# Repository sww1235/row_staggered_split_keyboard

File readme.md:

# Row Staggered Split Keyboard

The Row Staggered Split keyboard is for typists who need to maintain their muscle memory
of standard ANSI layout 104 key keyboards, but also would like a split keyboard.

This keyboard consists of 4 large components that are completely independant but augment each other:

- Left hand keyboard
- Right hand keyboard
- Navigation cluster
- Numpad

All components of the keyboard have independant KB2040 controllers and so do
not use the split keyboard functionality in QMK.

All keyboard components have per key RGB LED matrix lighting.

These keyboards have first class support in QMK. VIA/VIAL support is not
available currently as I do not use it, but there is nothing restricting its
addition in the future.

## Left Hand Keyboard

This is the left side of a standard ANSI 104 key layout keyboard, including the
`B` key. The `ESC` key and `F1`-`F4` are in their usual locations, and
`F5`-`F10` are in an additional row to the left of the `Tab`/`Shift`/`Caps
Lock` keys.

A `FN` key is included in the bottom right to provide alternate functionality
such as media keys, etc which are currently unimplemented. The `FN` layout
currently has additional keys defined for control of the RGB matrix, including
the `EE_CLR` key. This is needed to clear the keyboards EEPROM, primarily for
changing the RGB LED lighting effects.

## Right Hand Keyboard

This is the right side of a standard ANSI 104 key layout keyboard, including
the `B` key. As the left hand side has `F1`-`F10`, the function keys on the top
row start at `F11` and continue to `F16`, with `F17` available on the bottom
right.

A `FN` key is included in the bottom right to provide alternate functionality
such as media keys, etc which are currently unimplemented. The `FN` layout
currently has additional keys defined for control of the RGB matrix, including
the `EE_CLR` key. This is needed to clear the keyboards EEPROM, primarily for
changing the RGB LED lighting effects.

See the keyboard layouts shown below for more details.

## Navigation Cluster

This keyboard PCB is currently under developement, with PCB and key layout not finalized.

This section is the navigation cluster of standard ANSI 104 key layout
keyboards, including the `INSERT`, `DELETE`, `HOME`, `END`, `PAGE UP` and `PAGE
DOWN` keys, and the arrow cluster. 

To increase the number of function keys available, a 4th column has been added
with `F21`-`F24`, as well as the empty row between the `DELETE`/`END`/`PAGE
DOWN` keys and the arrow cluster has been filled in with `F18`-`F20`. There are
also 3 unassigned keys in the layout currently as seen in the layout images.

This section is essentially a 5 row x 4 column macro pad.

## Numpad

This keyboard PCB is currently under developement, with PCB and key layout not finalized.

This is a standard numpad layout, with some minor tweaks to the layout of the
nav cluster (numlock off) layer, and the addition of a `00` key.

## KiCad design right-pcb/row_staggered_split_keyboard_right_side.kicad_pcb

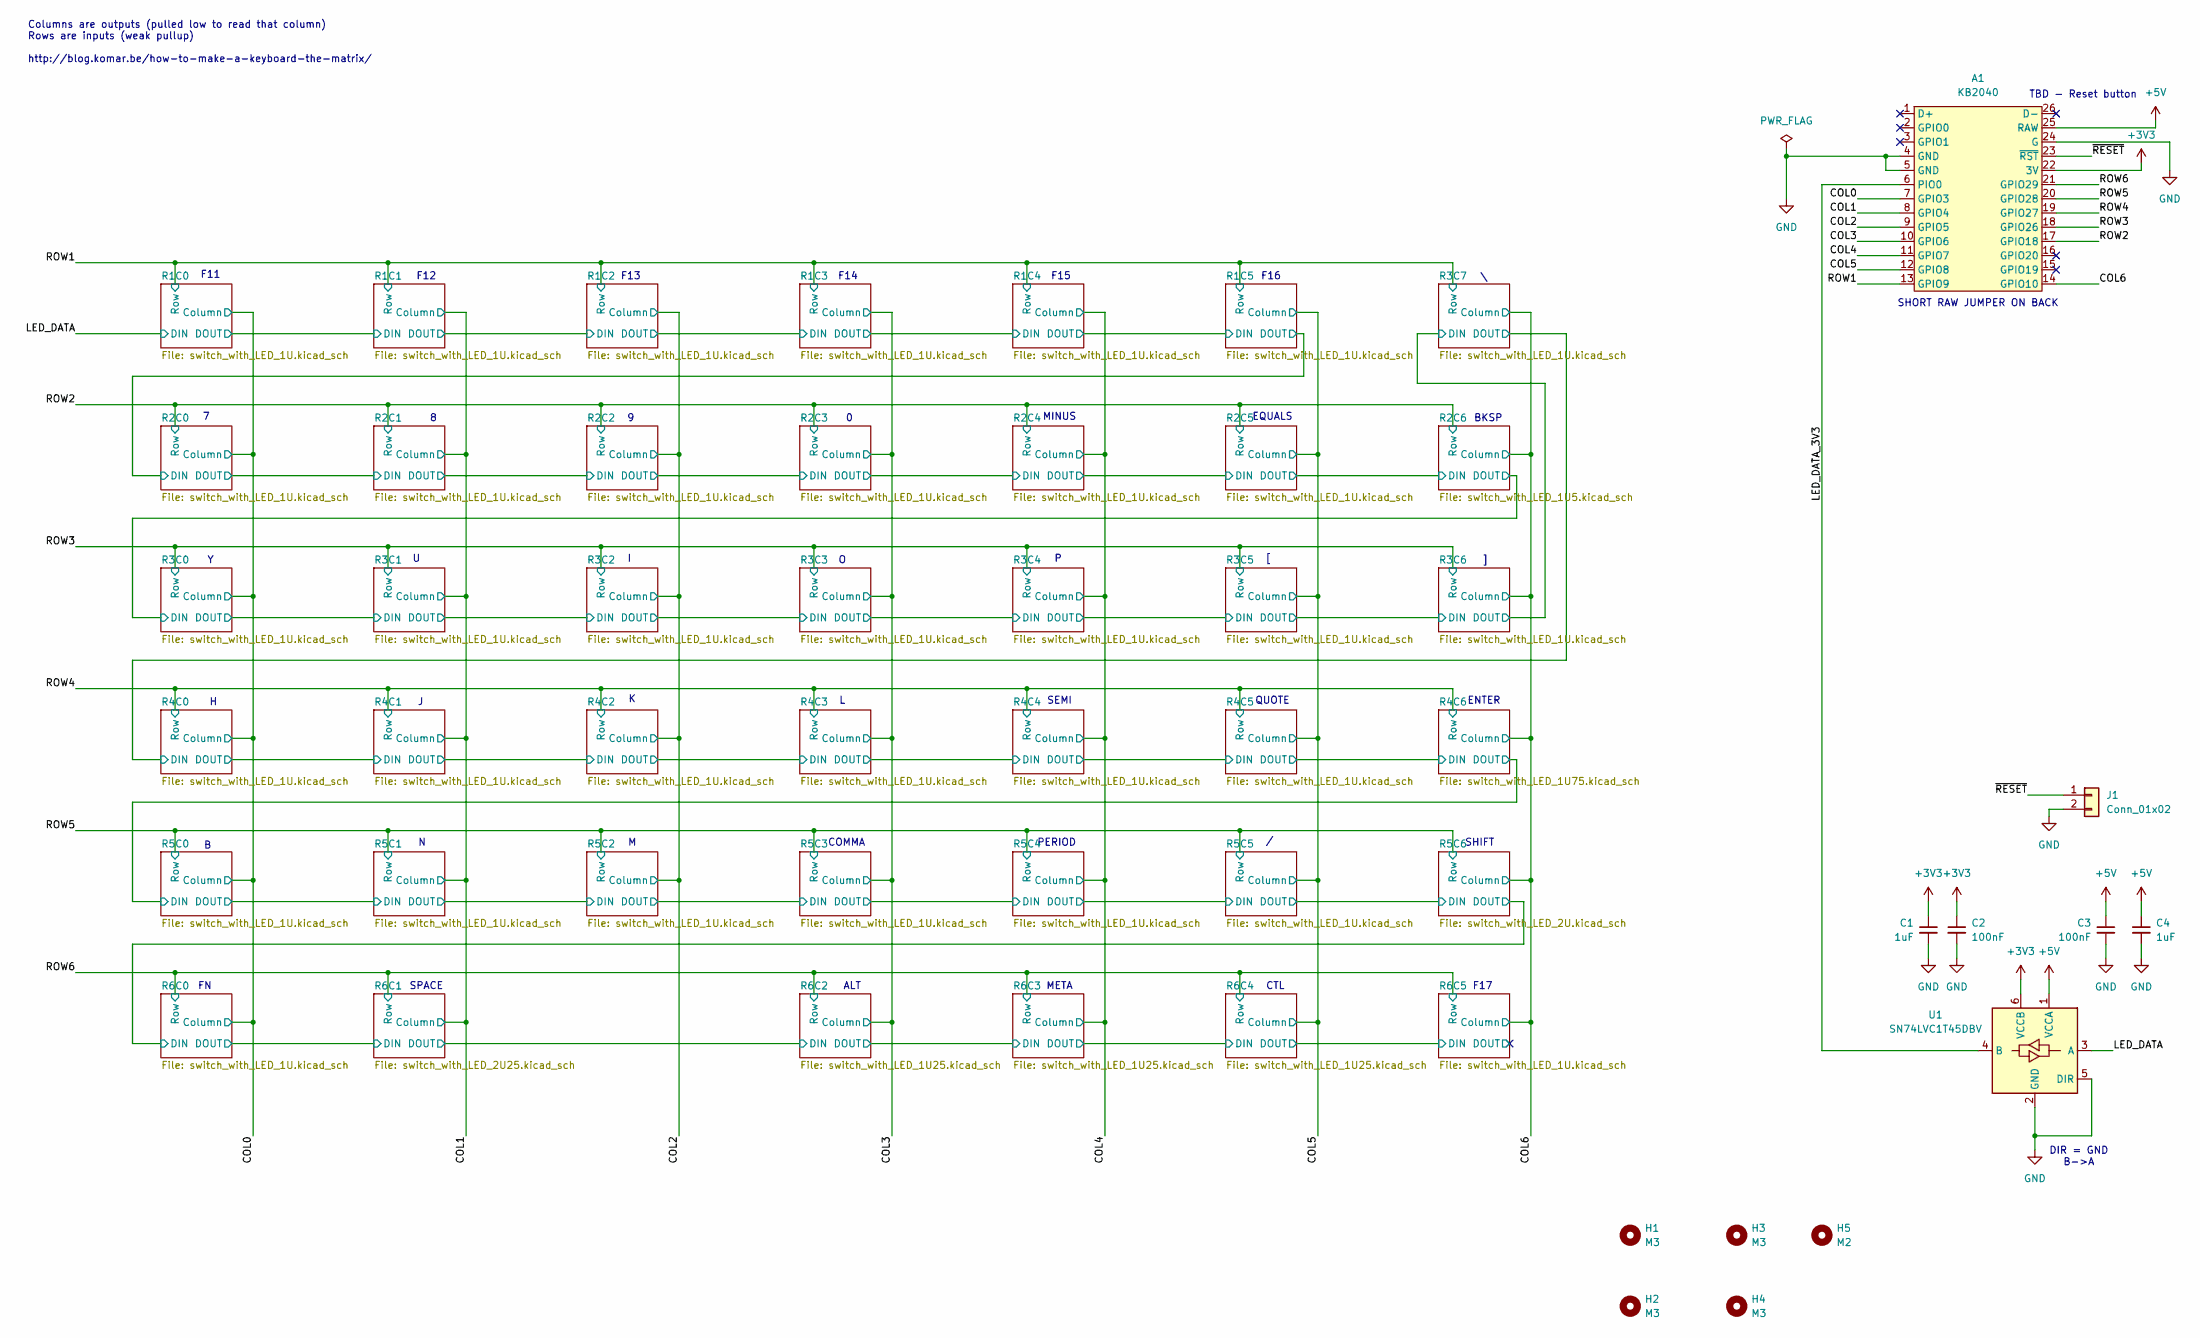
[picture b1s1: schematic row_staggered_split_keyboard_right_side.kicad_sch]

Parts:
A1: KB2040; KB2024_Socketed
C1, C4: 1uF; C_0805_2012Metric_Pad1.18x1.45mm_HandSolder
C2, C3: 100nF; C_0805_2012Metric_Pad1.18x1.45mm_HandSolder
H1, H2, H3, H4: M3; MountingHole_3.2mm_M3_ISO14580
H5: M2; MountingHole_2.2mm_M2
J1: Conn_01x02; PinSocket_1x02_P2.54mm_Vertical
U1: SN74LVC1T45DBV; SOT-23-6

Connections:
+3V3: A1.22 (3V), C1.1, C2.1, U1.6 (VCCB)
+5V: A1.25 (RAW), C3.1, C4.1, U1.1 (VCCA); also elsewhere on the board
/COL0: A1.7 (GPIO3); also elsewhere on the board
/COL1: A1.8 (GPIO4); also elsewhere on the board
/COL2: A1.9 (GPIO5); also elsewhere on the board
/COL3: A1.10 (GPIO6); also elsewhere on the board
/COL4: A1.11 (GPIO7); also elsewhere on the board
/COL5: A1.12 (GPIO8); also elsewhere on the board
/COL6: A1.14 (GPIO10); also elsewhere on the board
/LED_DATA: U1.3 (A); also elsewhere on the board
/LED_DATA_3V3: A1.6 (PIO0), U1.4 (B)
/ROW1: A1.13 (GPIO9); also elsewhere on the board
/ROW2: A1.17 (GPIO18); also elsewhere on the board
/ROW3: A1.18 (GPIO26); also elsewhere on the board
/ROW4: A1.19 (GPIO27); also elsewhere on the board
/ROW5: A1.20 (GPIO28); also elsewhere on the board
/ROW6: A1.21 (GPIO29); also elsewhere on the board
/~RESET: A1.23 (~RST), J1.1
GND: A1.4 (GND), A1.5 (GND), A1.24 (G), C1.2, C2.2, C3.2, C4.2, J1.2, U1.2 (GND), U1.5 (DIR); also elsewhere on the board

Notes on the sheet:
SHORT RAW JUMPER ON BACK
SPACE
DIR = GND B->A
ENTER
SHIFT
EQUALS
BKSP
F14
F15
META
MINUS
CTL
ALT
COMMA
QUOTE
F12
SEMI
F17
F13
F16
PERIOD
TBD - Reset button
Columns are outputs (pulled low to read that column) Rows are inputs (weak pullup) http://blog.komar.be/how-to-make-a-keyboard-the-matrix/
F11

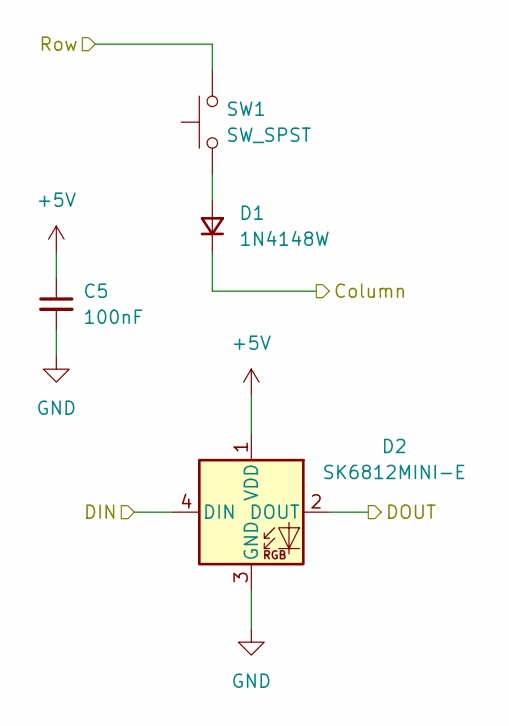
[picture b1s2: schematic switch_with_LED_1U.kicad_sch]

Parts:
C5: 100nF; C_0805_2012Metric_Pad1.18x1.45mm_HandSolder
D1: 1N4148W; D_SOD-123
D2: SK6812MINI-E; LED_SK6812MINI-E_REVERSE_MOUNT_3.2x2.8mm_P1.09mm
SW1: SW_SPST; SW_Hotswap_Kailh_MX_1.00u

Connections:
+5V: C5.1, D2.1 (VDD); also elsewhere on the board
/COL0: D1.1 (K); also elsewhere on the board
/LED_DATA: D2.4 (DIN); also elsewhere on the board
/R1C0/DOUT: D2.2 (DOUT); also elsewhere on the board
/ROW1: SW1.2; also elsewhere on the board
GND: C5.2, D2.3 (GND); also elsewhere on the board
unnamed: D1.2 (A), SW1.1

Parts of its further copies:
C6, C7, C8, C9, C10, C11, C12, C13, C14, C15, C16, C18, C19, C20, C21, C22, C23, C24, C25, C26, C27, C28, C29, C30, C31, C33, C34, C35, C36, C37, C38, C40, C45: 100nF; C_0805_2012Metric_Pad1.18x1.45mm_HandSolder
D3, D5, D7, D9, D11, D13, D15, D17, D19, D21, D23, D27, D29, D31, D33, D35, D37, D39, D41, D43, D45, D47, D49, D51, D53, D57, D59, D61, D63, D65, D67, D71, D81: 1N4148W; D_SOD-123
D4, D6, D8, D10, D12, D14, D16, D18, D20, D22, D24, D28, D30, D32, D34, D36, D38, D40, D42, D44, D46, D48, D50, D52, D54, D58, D60, D62, D64, D66, D68, D72, D82: SK6812MINI-E; LED_SK6812MINI-E_REVERSE_MOUNT_3.2x2.8mm_P1.09mm
SW2, SW3, SW4, SW5, SW6, SW7, SW8, SW9, SW10, SW11, SW12, SW14, SW15, SW16, SW17, SW18, SW19, SW20, SW21, SW22, SW23, SW24, SW25, SW26, SW27, SW29, SW30, SW31, SW32, SW33, SW34, SW36, SW41: SW_SPST; SW_Hotswap_Kailh_MX_1.00u

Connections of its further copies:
+5V: C6.1, C7.1, C8.1, C9.1, C10.1, C11.1, C12.1, C13.1, C14.1, C15.1, C16.1, C18.1, C19.1, C20.1, C21.1, C22.1, C23.1, C24.1, C25.1, C26.1, C27.1, C28.1, C29.1, C30.1, C31.1, C33.1, C34.1, C35.1, C36.1, C37.1, C38.1, C40.1, C45.1, D4.1 (VDD), D6.1 (VDD), D8.1 (VDD), D10.1 (VDD), D12.1 (VDD), D14.1 (VDD), D16.1 (VDD), D18.1 (VDD), D20.1 (VDD), D22.1 (VDD), D24.1 (VDD), D28.1 (VDD), D30.1 (VDD), D32.1 (VDD), D34.1 (VDD), D36.1 (VDD), D38.1 (VDD), D40.1 (VDD), D42.1 (VDD), D44.1 (VDD), D46.1 (VDD), D48.1 (VDD), D50.1 (VDD), D52.1 (VDD), D54.1 (VDD), D58.1 (VDD), D60.1 (VDD), D62.1 (VDD), D64.1 (VDD), D66.1 (VDD), D68.1 (VDD), D72.1 (VDD), D82.1 (VDD); also elsewhere on the board
/COL0: D13.1 (K), D27.1 (K), D43.1 (K), D57.1 (K), D71.1 (K); also elsewhere on the board
/COL1: D3.1 (K), D15.1 (K), D29.1 (K), D45.1 (K), D59.1 (K); also elsewhere on the board
/COL2: D5.1 (K), D17.1 (K), D31.1 (K), D47.1 (K), D61.1 (K); also elsewhere on the board
/COL3: D7.1 (K), D19.1 (K), D33.1 (K), D49.1 (K), D63.1 (K); also elsewhere on the board
/COL4: D9.1 (K), D21.1 (K), D35.1 (K), D51.1 (K), D65.1 (K); also elsewhere on the board
/COL5: D11.1 (K), D23.1 (K), D37.1 (K), D53.1 (K), D67.1 (K); also elsewhere on the board
/COL6: D39.1 (K), D41.1 (K), D81.1 (K); also elsewhere on the board
/R1C0/DOUT: D4.4 (DIN); also elsewhere on the board
/R1C1/DOUT: D4.2 (DOUT), D6.4 (DIN)
/R1C2/DOUT: D6.2 (DOUT), D8.4 (DIN)
/R1C3/DOUT: D8.2 (DOUT), D10.4 (DIN)
/R1C4/DOUT: D10.2 (DOUT), D12.4 (DIN)
/R1C5/DOUT: D12.2 (DOUT), D14.4 (DIN)
/R2C0/DOUT: D14.2 (DOUT), D16.4 (DIN)
/R2C1/DOUT: D16.2 (DOUT), D18.4 (DIN)
/R2C2/DOUT: D18.2 (DOUT), D20.4 (DIN)
/R2C3/DOUT: D20.2 (DOUT), D22.4 (DIN)
/R2C4/DOUT: D22.2 (DOUT), D24.4 (DIN)
/R2C5/DOUT: D24.2 (DOUT); also elsewhere on the board
/R2C6/DOUT: D28.4 (DIN); also elsewhere on the board
/R3C0/DOUT: D28.2 (DOUT), D30.4 (DIN)
/R3C1/DOUT: D30.2 (DOUT), D32.4 (DIN)
/R3C2/DOUT: D32.2 (DOUT), D34.4 (DIN)
/R3C3/DOUT: D34.2 (DOUT), D36.4 (DIN)
/R3C4/DOUT: D36.2 (DOUT), D38.4 (DIN)
/R3C5/DOUT: D38.2 (DOUT), D40.4 (DIN)
/R3C6/DOUT: D40.2 (DOUT), D42.4 (DIN)
/R3C7/DOUT: D42.2 (DOUT), D44.4 (DIN)
/R4C0/DOUT: D44.2 (DOUT), D46.4 (DIN)
/R4C1/DOUT: D46.2 (DOUT), D48.4 (DIN)
/R4C2/DOUT: D48.2 (DOUT), D50.4 (DIN)
/R4C3/DOUT: D50.2 (DOUT), D52.4 (DIN)
/R4C4/DOUT: D52.2 (DOUT), D54.4 (DIN)
/R4C5/DOUT: D54.2 (DOUT); also elsewhere on the board
/R4C6/DOUT: D58.4 (DIN); also elsewhere on the board
/R5C0/DOUT: D58.2 (DOUT), D60.4 (DIN)
/R5C1/DOUT: D60.2 (DOUT), D62.4 (DIN)
/R5C2/DOUT: D62.2 (DOUT), D64.4 (DIN)
/R5C3/DOUT: D64.2 (DOUT), D66.4 (DIN)
/R5C4/DOUT: D66.2 (DOUT), D68.4 (DIN)
/R5C5/DOUT: D68.2 (DOUT); also elsewhere on the board
/R5C6/DOUT: D72.4 (DIN); also elsewhere on the board
/R6C0/DOUT: D72.2 (DOUT); also elsewhere on the board
/R6C4/DOUT: D82.4 (DIN); also elsewhere on the board
/R6C5/DOUT: D82.2 (DOUT)
/ROW1: SW2.2, SW3.2, SW4.2, SW5.2, SW6.2, SW21.2; also elsewhere on the board
/ROW2: SW7.2, SW8.2, SW9.2, SW10.2, SW11.2, SW12.2; also elsewhere on the board
/ROW3: SW14.2, SW15.2, SW16.2, SW17.2, SW18.2, SW19.2, SW20.2; also elsewhere on the board
/ROW4: SW22.2, SW23.2, SW24.2, SW25.2, SW26.2, SW27.2; also elsewhere on the board
/ROW5: SW29.2, SW30.2, SW31.2, SW32.2, SW33.2, SW34.2; also elsewhere on the board
/ROW6: SW36.2, SW41.2; also elsewhere on the board
GND: C6.2, C7.2, C8.2, C9.2, C10.2, C11.2, C12.2, C13.2, C14.2, C15.2, C16.2, C18.2, C19.2, C20.2, C21.2, C22.2, C23.2, C24.2, C25.2, C26.2, C27.2, C28.2, C29.2, C30.2, C31.2, C33.2, C34.2, C35.2, C36.2, C37.2, C38.2, C40.2, C45.2, D4.3 (GND), D6.3 (GND), D8.3 (GND), D10.3 (GND), D12.3 (GND), D14.3 (GND), D16.3 (GND), D18.3 (GND), D20.3 (GND), D22.3 (GND), D24.3 (GND), D28.3 (GND), D30.3 (GND), D32.3 (GND), D34.3 (GND), D36.3 (GND), D38.3 (GND), D40.3 (GND), D42.3 (GND), D44.3 (GND), D46.3 (GND), D48.3 (GND), D50.3 (GND), D52.3 (GND), D54.3 (GND), D58.3 (GND), D60.3 (GND), D62.3 (GND), D64.3 (GND), D66.3 (GND), D68.3 (GND), D72.3 (GND), D82.3 (GND); also elsewhere on the board
unnamed: D3.2 (A), SW2.1
unnamed: D5.2 (A), SW3.1
unnamed: D7.2 (A), SW4.1
unnamed: D9.2 (A), SW5.1
unnamed: D11.2 (A), SW6.1
unnamed: D13.2 (A), SW7.1
unnamed: D15.2 (A), SW8.1
unnamed: D17.2 (A), SW9.1
unnamed: D19.2 (A), SW10.1
unnamed: D21.2 (A), SW11.1
unnamed: D23.2 (A), SW12.1
unnamed: D27.2 (A), SW14.1
unnamed: D29.2 (A), SW15.1
unnamed: D31.2 (A), SW16.1
unnamed: D33.2 (A), SW17.1
unnamed: D35.2 (A), SW18.1
unnamed: D37.2 (A), SW19.1
unnamed: D39.2 (A), SW20.1
unnamed: D41.2 (A), SW21.1
unnamed: D43.2 (A), SW22.1
unnamed: D45.2 (A), SW23.1
unnamed: D47.2 (A), SW24.1
unnamed: D49.2 (A), SW25.1
unnamed: D51.2 (A), SW26.1
unnamed: D53.2 (A), SW27.1
unnamed: D57.2 (A), SW29.1
unnamed: D59.2 (A), SW30.1
unnamed: D61.2 (A), SW31.1
unnamed: D63.2 (A), SW32.1
unnamed: D65.2 (A), SW33.1
unnamed: D67.2 (A), SW34.1
unnamed: D71.2 (A), SW36.1
unnamed: D81.2 (A), SW41.1

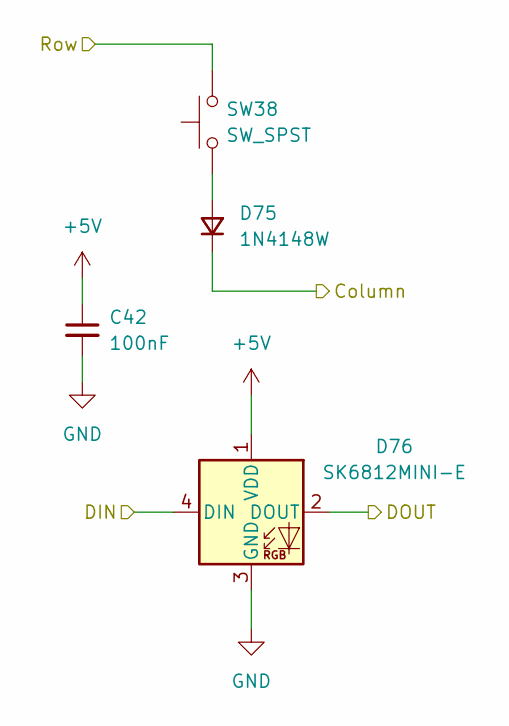
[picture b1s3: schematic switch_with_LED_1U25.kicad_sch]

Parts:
C42: 100nF; C_0805_2012Metric_Pad1.18x1.45mm_HandSolder
D75: 1N4148W; D_SOD-123
D76: SK6812MINI-E; LED_SK6812MINI-E_REVERSE_MOUNT_3.2x2.8mm_P1.09mm
SW38: SW_SPST; SW_Hotswap_Kailh_MX_1.25u

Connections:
+5V: C42.1, D76.1 (VDD); also elsewhere on the board
/COL3: D75.1 (K); also elsewhere on the board
/R6C1/DOUT: D76.4 (DIN); also elsewhere on the board
/R6C2/DOUT: D76.2 (DOUT); also elsewhere on the board
/ROW6: SW38.2; also elsewhere on the board
GND: C42.2, D76.3 (GND); also elsewhere on the board
unnamed: D75.2 (A), SW38.1

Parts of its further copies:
C43, C44: 100nF; C_0805_2012Metric_Pad1.18x1.45mm_HandSolder
D77, D79: 1N4148W; D_SOD-123
D78, D80: SK6812MINI-E; LED_SK6812MINI-E_REVERSE_MOUNT_3.2x2.8mm_P1.09mm
SW39, SW40: SW_SPST; SW_Hotswap_Kailh_MX_1.25u

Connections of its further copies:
+5V: C43.1, C44.1, D78.1 (VDD), D80.1 (VDD); also elsewhere on the board
/COL4: D77.1 (K); also elsewhere on the board
/COL5: D79.1 (K); also elsewhere on the board
/R6C2/DOUT: D78.4 (DIN); also elsewhere on the board
/R6C3/DOUT: D78.2 (DOUT), D80.4 (DIN)
/R6C4/DOUT: D80.2 (DOUT); also elsewhere on the board
/ROW6: SW39.2, SW40.2; also elsewhere on the board
GND: C43.2, C44.2, D78.3 (GND), D80.3 (GND); also elsewhere on the board
unnamed: D77.2 (A), SW39.1
unnamed: D79.2 (A), SW40.1

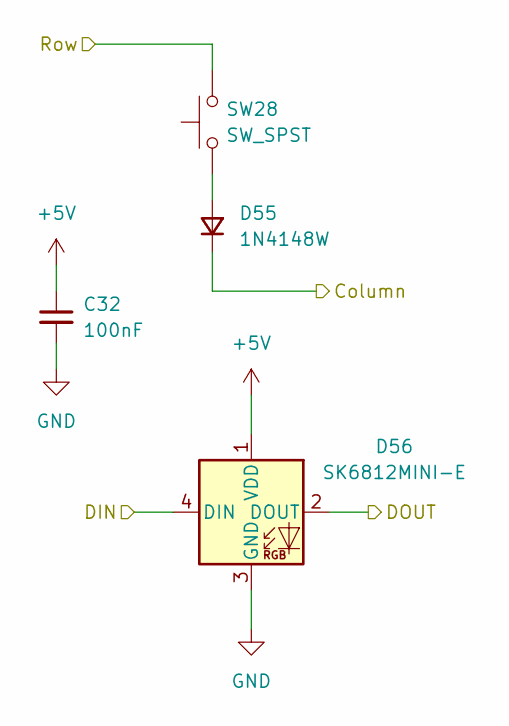
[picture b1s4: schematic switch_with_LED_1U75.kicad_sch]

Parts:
C32: 100nF; C_0805_2012Metric_Pad1.18x1.45mm_HandSolder
D55: 1N4148W; D_SOD-123
D56: SK6812MINI-E; LED_SK6812MINI-E_REVERSE_MOUNT_3.2x2.8mm_P1.09mm
SW28: SW_SPST; SW_Hotswap_Kailh_MX_1.75u

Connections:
+5V: C32.1, D56.1 (VDD); also elsewhere on the board
/COL6: D55.1 (K); also elsewhere on the board
/R4C5/DOUT: D56.4 (DIN); also elsewhere on the board
/R4C6/DOUT: D56.2 (DOUT); also elsewhere on the board
/ROW4: SW28.2; also elsewhere on the board
GND: C32.2, D56.3 (GND); also elsewhere on the board
unnamed: D55.2 (A), SW28.1

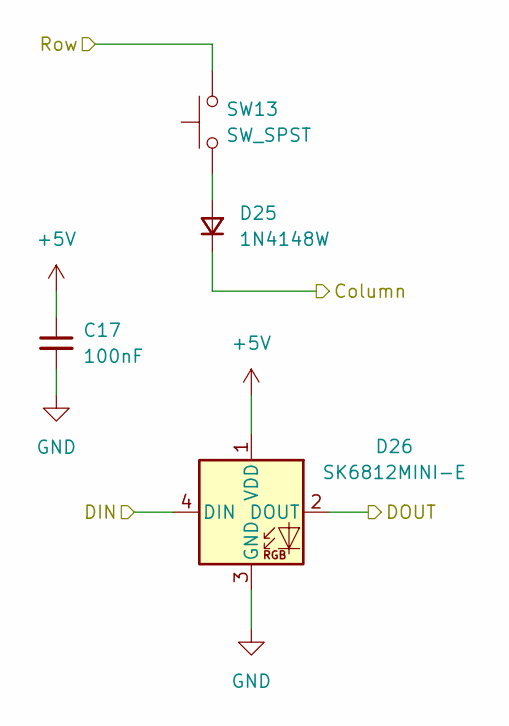
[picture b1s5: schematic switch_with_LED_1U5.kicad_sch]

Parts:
C17: 100nF; C_0805_2012Metric_Pad1.18x1.45mm_HandSolder
D25: 1N4148W; D_SOD-123
D26: SK6812MINI-E; LED_SK6812MINI-E_REVERSE_MOUNT_3.2x2.8mm_P1.09mm
SW13: SW_SPST; SW_Hotswap_Kailh_MX_1.50u

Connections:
+5V: C17.1, D26.1 (VDD); also elsewhere on the board
/COL6: D25.1 (K); also elsewhere on the board
/R2C5/DOUT: D26.4 (DIN); also elsewhere on the board
/R2C6/DOUT: D26.2 (DOUT); also elsewhere on the board
/ROW2: SW13.2; also elsewhere on the board
GND: C17.2, D26.3 (GND); also elsewhere on the board
unnamed: D25.2 (A), SW13.1

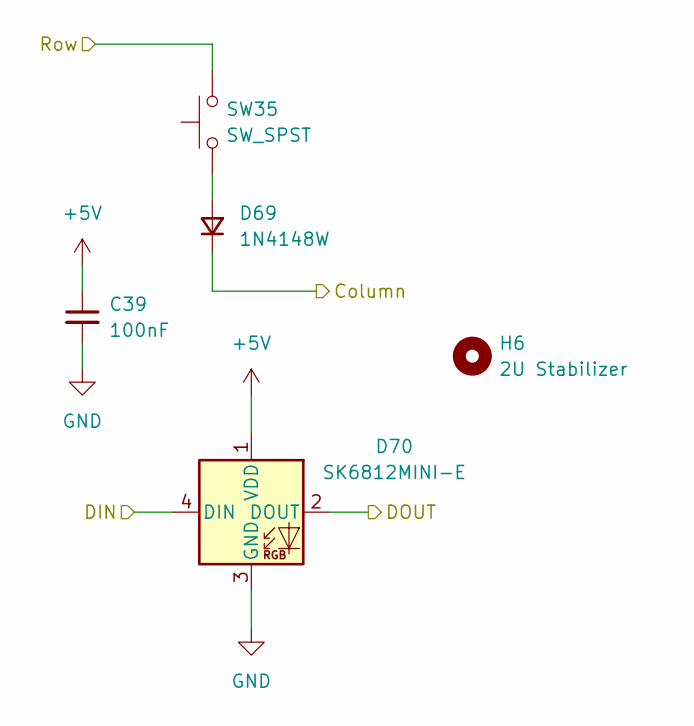
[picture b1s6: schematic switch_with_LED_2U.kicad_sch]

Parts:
C39: 100nF; C_0805_2012Metric_Pad1.18x1.45mm_HandSolder
D69: 1N4148W; D_SOD-123
D70: SK6812MINI-E; LED_SK6812MINI-E_REVERSE_MOUNT_3.2x2.8mm_P1.09mm
H6: 2U Stabilizer; Stabilizer_Cherry_MX_2.00u
SW35: SW_SPST; SW_Hotswap_Kailh_MX_2.00u

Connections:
+5V: C39.1, D70.1 (VDD); also elsewhere on the board
/COL6: D69.1 (K); also elsewhere on the board
/R5C5/DOUT: D70.4 (DIN); also elsewhere on the board
/R5C6/DOUT: D70.2 (DOUT); also elsewhere on the board
/ROW5: SW35.2; also elsewhere on the board
GND: C39.2, D70.3 (GND); also elsewhere on the board
unnamed: D69.2 (A), SW35.1

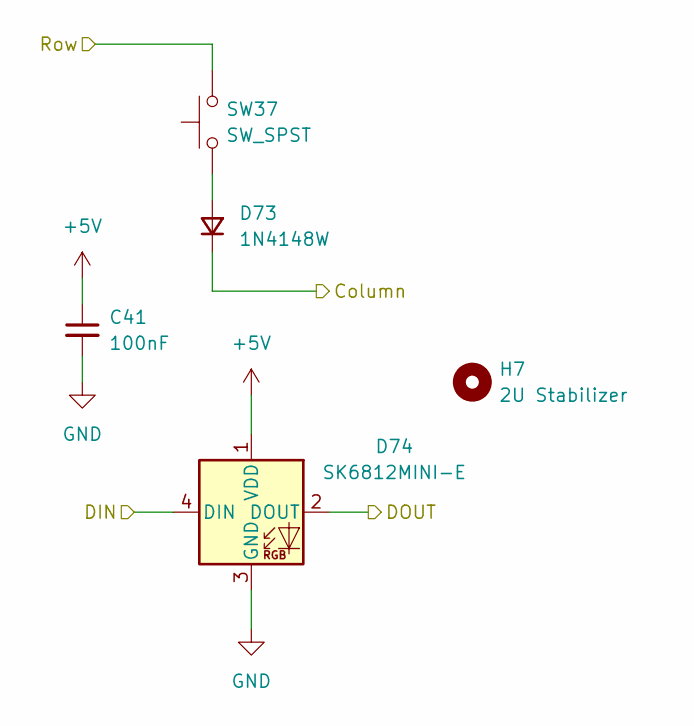
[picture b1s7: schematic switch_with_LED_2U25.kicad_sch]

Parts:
C41: 100nF; C_0805_2012Metric_Pad1.18x1.45mm_HandSolder
D73: 1N4148W; D_SOD-123
D74: SK6812MINI-E; LED_SK6812MINI-E_REVERSE_MOUNT_3.2x2.8mm_P1.09mm
H7: 2U Stabilizer; Stabilizer_Cherry_MX_2.00u
SW37: SW_SPST; SW_Hotswap_Kailh_MX_2.25u

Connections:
+5V: C41.1, D74.1 (VDD); also elsewhere on the board
/COL1: D73.1 (K); also elsewhere on the board
/R6C0/DOUT: D74.4 (DIN); also elsewhere on the board
/R6C1/DOUT: D74.2 (DOUT); also elsewhere on the board
/ROW6: SW37.2; also elsewhere on the board
GND: C41.2, D74.3 (GND); also elsewhere on the board
unnamed: D73.2 (A), SW37.1

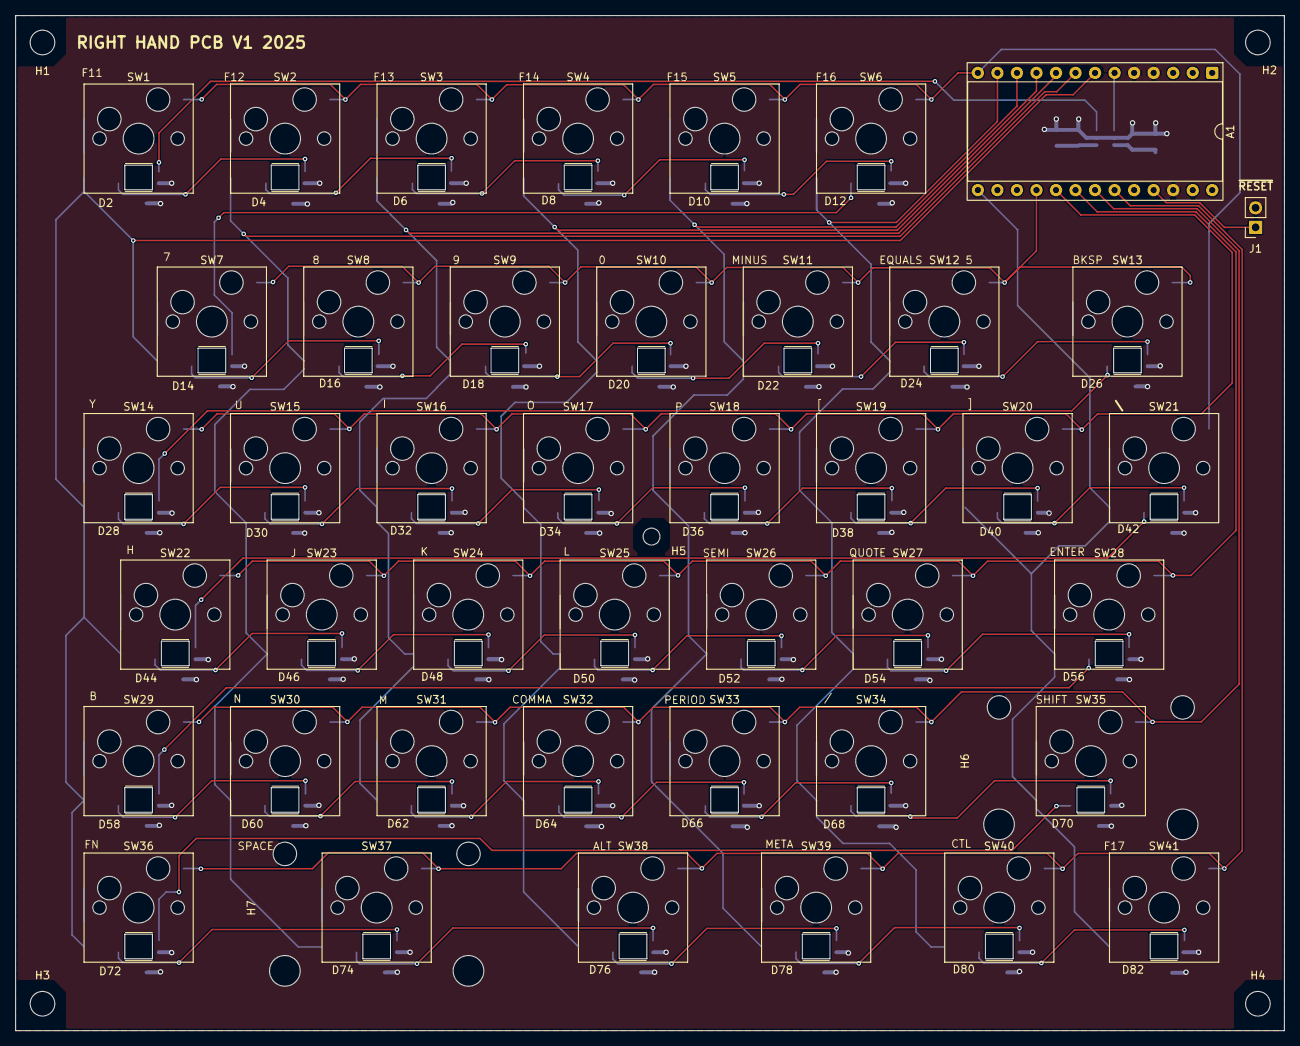
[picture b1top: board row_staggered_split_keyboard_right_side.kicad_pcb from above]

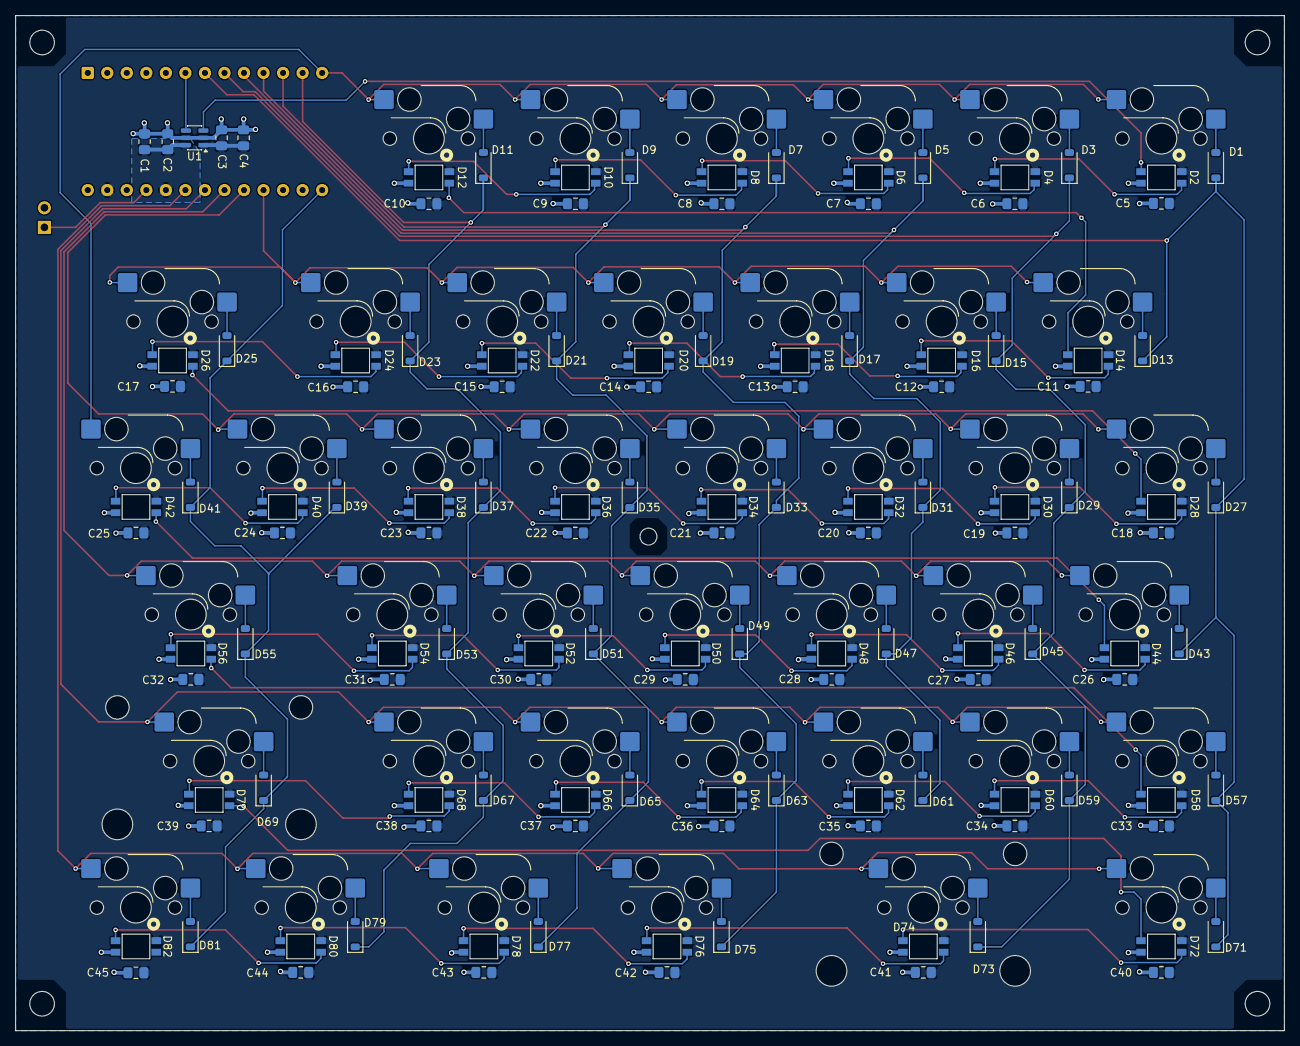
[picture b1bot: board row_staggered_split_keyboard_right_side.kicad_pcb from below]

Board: 2 copper layers, 165.0 x 132.0 mm, 178 parts (87 on the bottom side), 100 nets.

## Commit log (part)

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2025-10-16 initial commit of schematic and pcb
2025-10-18 renamed files anticipating right side project
2025-10-19 Updating schematic with different size keys
    Also updated LED data wiring to correspond with PCB layout
2025-10-20 Next revision of PCB
2025-10-21 Initial modifications to reduce fab cost and add caps
    Removing 1 row and column of keys, and majorly changing layout
    Routing still in progress
2025-10-22 Caps, shrunk board, added mounting holes
2025-10-22 Added exterior dimension indication to board
2025-10-29 Adding values to Diodes and adding stabilizers to 2U switches
2025-10-29 forgot to update diode values in PCB
2025-10-30 Added extra column to left hand keyboard
    Matching size to right hand side.
2025-11-02 locked mounting hole positions and board edges
2025-11-02 initial commit of right hand pcb
2025-11-02 adding keyboard layout description file
2025-11-02 initial placement of switches and modifications from left to right
2025-11-03 a bunch of DRC fixes and pcb work
2025-11-03 locking edge_cuts and holes
2025-11-03 reworking LED data lines to eliminate ground plane disconnections
2025-11-03 duplicate track cleanup and avoiding silkscreen with tracks
2025-11-09 Silkscreen cleanup and trace cleanup in prep for PCB review posting
2025-11-09 adding SVGs of schematic and PCB used for v1 review
2025-11-09 updating project file
2025-11-09 ignored generated PNGs
2025-11-09 Added keyboard-layout-editor.com json files for left and right hand
2026-02-21 applied feedback from coworker
2026-05-27 updating for KiCAD 10.0
2026-05-29 adding mounting hole in center for additional support, and cleaning up tracks/zones
2026-05-31 ignoring generated gerber files
2026-05-31 fixed that some components were not included in the BOM
2026-06-20 Boards were ordered
